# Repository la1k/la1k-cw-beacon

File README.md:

LA1K CW beacon project
======================

A 35-4400 MHz CW exciter design on a 75 x 45 mm 4-layer PCB. Will initially be used for a 70 MHz beacon in Norway (with a 25 W PA and an external 10 MHz OCXO), and eventually replace hardware in our existing 2m and 70cm beacons. A serial port is used for configuration of callsign, ramp time, frequency etc.

- **Microcontroller (Microchip PIC18F26K22):** Controls synthesizer, does CW timing, controls VGA gain.
- **Synthesizer (Analog Devices ADF4351):** Fractional-N synthesizer with VCO which generates the RF-signal. Only course control over output power.
- **VGA (Analog Devices ADL5330):** Amplifier with variable gain over a 60 dB span. Controlled by filtered PWM-signal from microcontroller and softens the keying transitions by controlling output power ramping. Also works as a buffer for an external PA.

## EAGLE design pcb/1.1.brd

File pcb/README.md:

- BOM is located in this folder in CSV and tab-separated formats. 
- Most components have vendor part numbers from Digi-Key.
- Reference oscillator FOX924B, C40 and C38 is typically not inserted if used with external oscillator, as there will be some leakage over the REF_SEL header even without a jumper installed.
- For PCB 1.0, remember to scratch away solder stop mask for U1 and U2 exposed pads.
- Use standard 0.1" / 2.54 mm pitch break-away headers for PIC_GPIO, PIC_UART, REF_SEL and PIC_REF.

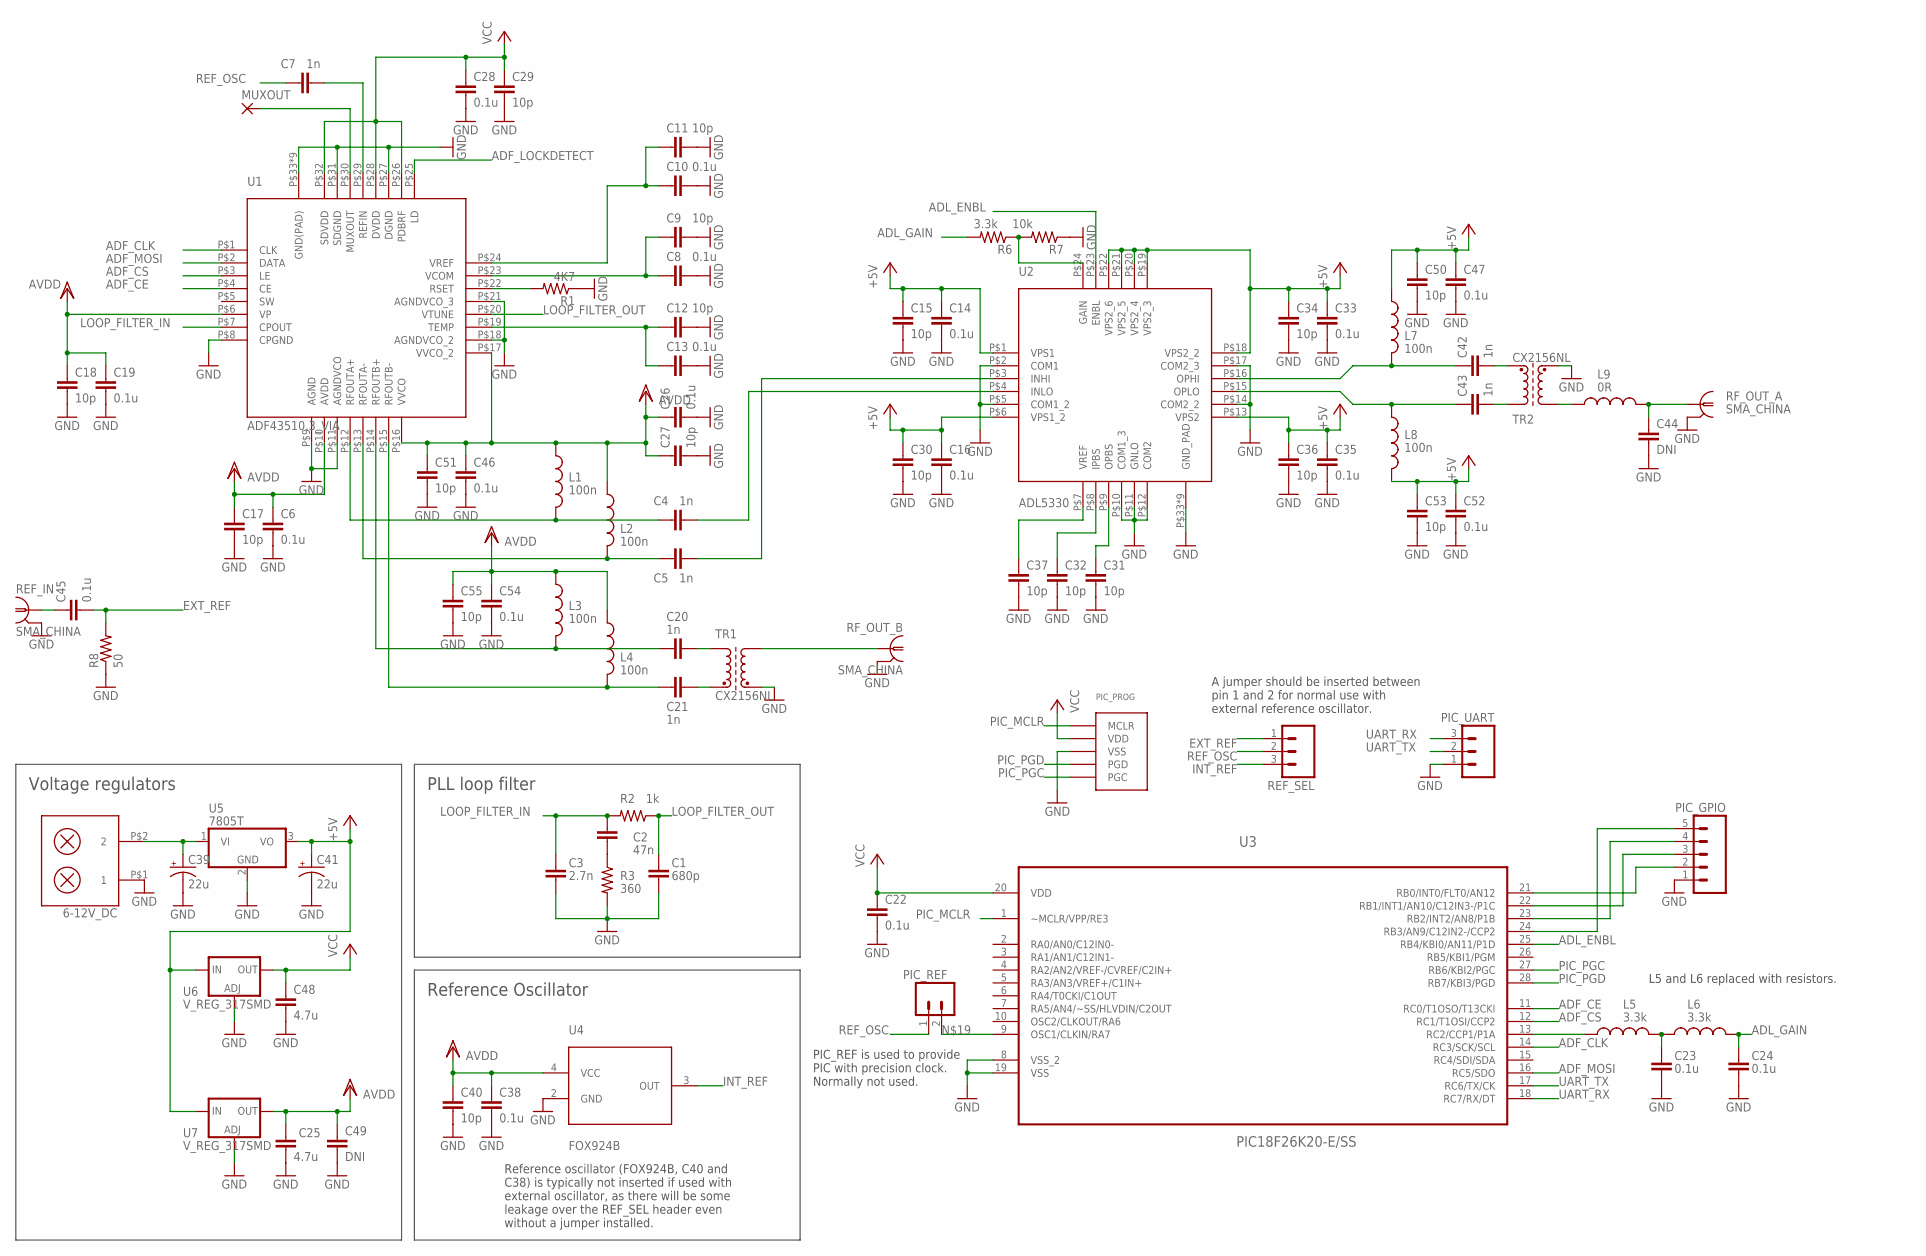
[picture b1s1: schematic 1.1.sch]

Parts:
6-12V_DC: PK5602; PARTNO 1984617
C1: 680p; 0603-CAP; PARTNO GRM1885C1H681JA01D
C2: 47n; 0603-CAP; PARTNO GRM188R71E473JA01D
C3: 2.7n; 0603-CAP; PARTNO GRM1885C1H272JA01D
C4, C5, C7, C20, C21: 1n; 0603-CAP; PARTNO GRM1885C1H102FA01D
C6, C8, C10, C13, C14, C16, C19, C22, C23, C24, C26, C28, C33, C35, C38, C45, C46, C47, C52, C54: 0.1u; 0603-CAP; PARTNO GRM188R71E104KA01D
C9, C11, C12, C15, C17, C18, C27, C29, C30, C31, C32, C34, C36, C37, C40, C50, C51, C53, C55: 10p; 0603-CAP; PARTNO GRM1885C1H100FA01D
C25, C48: 4.7u; C0805; PARTNO GRM21BR61E475KA12K
C39, C41: 22u; VISHAY_C; PARTNO TH4C226K016C1400
C42, C43: 1n; C0805K; PARTNO GRM1885C1H102FA01D
C44: DNI; C0805K; PARTNO *
C49: DNI; C0805; PARTNO *
L1, L2, L3, L4: 100n; 0603; PARTNO LQW18ANR10J00D
L5, L6: 3.3k; 0603; PARTNO MCR03ERTF3321
L7, L8: 100n; C0805K; PARTNO LQW18ANR10J00D
L9: 0R; C0805K; PARTNO *
MUXOUT: SMD2; SMD1,27-2,54; PARTNO *
PIC_GPIO: M05PTH; 1X05; PARTNO *
PIC_PROG: 1X5_ICSP; 1X5_2MM; PARTNO M22-2510505
PIC_REF: M02PTH; 1X02; PARTNO *
PIC_UART: M03PTH; 1X03; PARTNO *
R1: 4K7; 0603-RES; PARTNO MCR03ERTF4701
R2: 1k; 0603-RES; PARTNO MCR03ERTF1001
R3: 360; 0603-RES; PARTNO MCR03ERTF3600
R6: 3.3k; 0603-RES; PARTNO MCR03ERTF3321
R7: 10k; 0603-RES; PARTNO MCR03ERTF1002
R8: 50; C0805K; PARTNO ERJ-P06J510V
REF_IN: SMA_CHINA; SMA-EDGE; PARTNO SMA-J-P-H-ST-EM1
REF_SEL: M03PTH; 1X03; PARTNO *
RF_OUT_A: SMA_CHINA; SMA-EDGE; PARTNO SMA-J-P-H-ST-EM1
RF_OUT_B: SMA_CHINA; SMA-EDGE; PARTNO SMA-J-P-H-ST-EM1
TR1, TR2: CX2156NL; PARTNO CX2156NL
U1: ADF43510.3_VIA; LFCSP_CP-32-2_.3VIA; PARTNO ADF4351BCPZ-RL7
U2: ADL5330; LFCSP_CP-24-2_.3VIA; PARTNO ADL5330ACPZ-REEL7
U3: PIC18F26K20-E/SS; SOP65P780X200-28N; PARTNO PIC18F26K22-I/SS
U4: FOX924B; PARTNO *
U5: 7805T; TO220H; PARTNO LM7805CT
U6, U7: V_REG_317SMD; SOT223; PARTNO AP2114H-3.3TRG1

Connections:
+5V: C14.1, C15.1, C16.1, C30.1, C33.1, C34.1, C35.1, C36.1, C41.+, C47.1, C50.1, C52.1, C53.1, L7.1, L8.1, U2.P$1 (VPS1), U2.P$6 (VPS1_2), U2.P$13 (VPS2), U2.P$18 (VPS2_2), U2.P$19 (VPS2_3), U2.P$20 (VPS2_4), U2.P$21 (VPS2_5), U2.P$22 (VPS2_6), U5.3 (VO), U6.3 (IN), U7.3 (IN)
ADF_CE: U1.P$4 (CE), U3.11 (RC0/T1OSO/T13CKI)
ADF_CLK: U1.P$1 (CLK), U3.14 (RC3/SCK/SCL)
ADF_CS: U1.P$3 (LE), U3.12 (RC1/T1OSI/CCP2)
ADF_LOCKDETECT: U1.P$25 (LD)
ADF_MOSI: U1.P$2 (DATA), U3.16 (RC5/SDO)
ADF_MUXOUT: MUXOUT.1, U1.P$30 (MUXOUT)
ADL_ENBL: U2.P$23 (ENBL), U3.25 (RB4/KBI0/AN11/P1D)
ADL_GAIN: C24.2, L6.2, R6.2
EXT_REF: C45.2, R8.2, REF_SEL.1
GND: 6-12V_DC.P$1 (1), C1.2, C3.2, C6.2, C8.2, C9.2, C10.2, C11.2, C12.2, C13.2, C14.2, C15.2, C16.2, C17.2, C18.2, C19.2, C22.2, C23.1, C24.1, C25.2, C26.2, C27.2, C28.2, C29.2, C30.2, C31.2, C32.2, C33.2, C34.2, C35.2, C36.2, C37.2, C38.2, C39.-, C40.2, C41.-, C44.2, C46.2, C47.2, C48.2, C49.2, C50.2, C51.2, C52.2, C53.2, C54.2, C55.2, PIC_GPIO.1, PIC_PROG.P$3 (VSS), PIC_UART.1, R1.1, R3.2, R7.1, R8.1, REF_IN.GND@0 (GND), REF_IN.GND@1 (GND), REF_IN.GND@2 (GND), REF_IN.GND@3 (GND), RF_OUT_A.GND@0 (GND), RF_OUT_A.GND@1 (GND), RF_OUT_A.GND@2 (GND), RF_OUT_A.GND@3 (GND), RF_OUT_B.GND@0 (GND), RF_OUT_B.GND@1 (GND), RF_OUT_B.GND@2 (GND), RF_OUT_B.GND@3 (GND), TR1.5 (E2), TR2.5 (E2), U1.P$8 (CPGND), U1.P$9 (AGND), U1.P$11 (AGNDVCO), U1.P$18 (AGNDVCO_2), U1.P$21 (AGNDVCO_3), U1.P$27 (DGND), U1.P$31 (SDGND), U1.P$33 (GND(PAD)), U1.P$34 (GND(PAD)), U1.P$35 (GND(PAD)), U1.P$36 (GND(PAD)), U1.P$37 (GND(PAD)), U1.P$38 (GND(PAD)), U1.P$39 (GND(PAD)), U1.P$40 (GND(PAD)), U1.P$41 (GND(PAD)), U2.P$2 (COM1), U2.P$5 (COM1_2), U2.P$10 (COM1_3), U2.P$11 (GNLO), U2.P$12 (COM2), U2.P$14 (COM2_2), U2.P$17 (COM2_3), U2.P$33 (GND_PAD), U2.P$34 (GND_PAD), U2.P$35 (GND_PAD), U2.P$36 (GND_PAD), U2.P$37 (GND_PAD), U2.P$38 (GND_PAD), U2.P$39 (GND_PAD), U2.P$40 (GND_PAD), U2.P$41 (GND_PAD), U3.8 (VSS_2), U3.19 (VSS), U4.2 (GND), U5.2 (GND), U6.1 (ADJ), U7.1 (ADJ)
INT_REF: REF_SEL.3, U4.3 (OUT)
LOOP_FILTER_IN: C2.1, C3.1, R2.2, U1.P$7 (CPOUT)
LOOP_FILTER_OUT: C1.1, R2.1, U1.P$20 (VTUNE)
unnamed: C5.2, U2.P$3 (INHI)
unnamed: C4.2, U2.P$4 (INLO)
unnamed: C7.2, U1.P$29 (REFIN)
unnamed: L9.1, TR2.4 (A2)
unnamed: C42.1, L7.2, U2.P$16 (OPHI)
unnamed: R1.2, U1.P$22 (RSET)
unnamed: C43.1, L8.2, U2.P$15 (OPLO)
unnamed: C2.2, R3.1
unnamed: C5.1, L2.2, U1.P$13 (RFOUTA-)
unnamed: C4.1, L1.2, U1.P$12 (RFOUTA+)
unnamed: 6-12V_DC.P$2 (2), C39.+, U5.1 (VI)
unnamed: C43.2, TR2.3 (A1)
unnamed: C12.1, C13.1, U1.P$19 (TEMP)
unnamed: C8.1, C9.1, U1.P$23 (VCOM)
unnamed: PIC_GPIO.5, U3.24 (RB3/AN9/C12IN2-/CCP2)
unnamed: C42.2, TR2.1 (E1)
unnamed: PIC_GPIO.4, U3.23 (RB2/INT2/AN8/P1B)
unnamed: C20.1, L3.2, U1.P$14 (RFOUTB+)
unnamed: PIC_REF.2, U3.9 (OSC1/CLKIN/RA7)
unnamed: C10.1, C11.1, U1.P$24 (VREF)
unnamed: C21.1, L4.2, U1.P$15 (RFOUTB-)
unnamed: L5.1, U3.13 (RC2/CCP1/P1A)
unnamed: C21.2, TR1.1 (E1)
unnamed: C23.2, L5.2, L6.1
unnamed: C20.2, TR1.3 (A1)
unnamed: RF_OUT_B.SIG (1), TR1.4 (A2)
unnamed: C37.1, U2.P$7 (VREF)
unnamed: PIC_GPIO.3, U3.22 (RB1/INT1/AN10/C12IN3-/P1C)
unnamed: PIC_GPIO.2, U3.21 (RB0/INT0/FLT0/AN12)
unnamed: R6.1, R7.2, U2.P$24 (GAIN)
unnamed: C45.1, REF_IN.SIG (1)
unnamed: C31.1, U2.P$9 (OPBS)
unnamed: C32.1, U2.P$8 (IPBS)
unnamed: C44.1, L9.2, RF_OUT_A.SIG (1)
PIC_MCLR: PIC_PROG.P$1 (MCLR), U3.1 (~MCLR/VPP/RE3)
PIC_PGC: PIC_PROG.P$5 (PGC), U3.27 (RB6/KBI2/PGC)
PIC_PGD: PIC_PROG.P$4 (PGD), U3.28 (RB7/KBI3/PGD)
REF_OSC: C7.1, PIC_REF.1, REF_SEL.2
UART_RX: PIC_UART.3, U3.18 (RC7/RX/DT)
UART_TX: PIC_UART.2, U3.17 (RC6/TX/CK)
VCC: C22.1, C28.1, C29.1, C48.1, PIC_PROG.P$2 (VDD), U1.P$26 (PDBRF), U1.P$28 (DVDD), U1.P$32 (SDVDD), U3.20 (VDD), U6.2 (OUT)
VDD: C6.1, C17.1, C18.1, C19.1, C25.1, C26.1, C27.1, C38.1, C40.1, C46.1, C49.1, C51.1, C54.1, C55.1, L1.1, L2.1, L3.1, L4.1, U1.P$6 (VP), U1.P$10 (AVDD), U1.P$16 (VVCO), U1.P$17 (VVCO_2), U4.4 (VCC), U7.2 (OUT)

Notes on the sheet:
PLL loop filter
Reference Oscillator
Voltage regulators
L5 and L6 replaced with resistors.
PIC_REF is used to provide PIC with precision clock. Normally not used.
A jumper should be inserted between pin 1 and 2 for normal use with external reference oscillator.
Reference oscillator (FOX924B, C40 and C38) is typically not inserted if used with external oscillator, as there will be some leakage over the REF_SEL header even without a jumper installed.

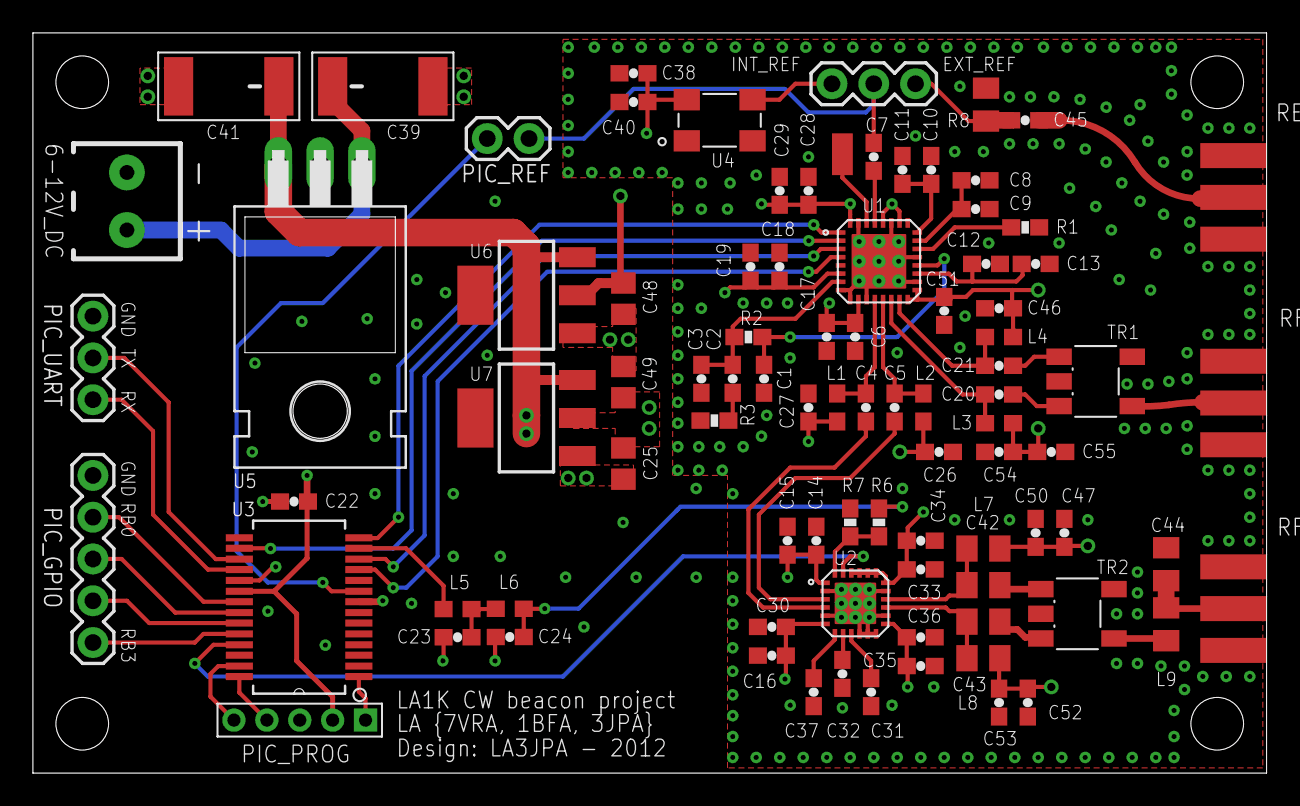
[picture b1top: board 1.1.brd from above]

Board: 4 copper layers, 75.0 x 45.0 mm, 89 parts (0 on the bottom side), 55 nets.

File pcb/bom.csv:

Mfg_PN,Mfg,Vendor_PN,Vendor,Description,Qty-1,Qty-5,Qty-25,Part References,Value
GRM188R71E104KA01D,Murata,490-1524-1-ND,Digikey,CAP CER 0.1UF 25V 10% X7R 0603,20,100,500,"C6, C8, C10, C13, C14, C16, C19, C22, C23, C24, C26, C28, C33, C35, C38, C45, C46, C47, C52, C54",0.1u
M22-2510505,Harwin,952-1314-ND,Digikey,CONN HEADER 2MM VERT AU 5POS,1,5,25,"PIC_PROG",1X5_ICSP
MCR03ERTF1001,Rohm,RHM1.00KCFCT-ND,Digikey,RES 1K OHM 1/10W 1% 0603 SMD,1,5,25,"R2",1k
GRM1885C1H102FA01D,Murata,490-6376-1-ND,Digikey,CAP CER 1000pF 50V 0603,2,10,50,"C42, C43",1n
GRM1885C1H102FA01D,Murata,490-6376-1-ND,Digikey,CAP CER 1000pF 50V 0603,5,25,125,"C4, C5, C7, C20, C21",1n
GRM1885C1H272JA01D,Murata,490-3283-1-ND,Digikey,CAP CER 2700pF 50V 0603,1,5,25,"C3",2.7n
MCR03ERTF3321,Rohm,RHM3.32KCFCT-ND,Digikey,RES 3.32K OHM 1/10W 1% 0603 SMD,2,10,50,"L5, L6",3.3k
MCR03ERTF3321,Rohm,RHM3.32KCFCT-ND,Digikey,RES 3.32K OHM 1/10W 1% 0603 SMD,1,5,25,"R6",3.3k
GRM21BR61E475KA12K,Murata,490-6475-1-ND,Digikey,CAP CER 4.7UF 25V 10% X5R 0805,2,10,50,"C25, C48",4.7u
MCR03ERTF4701,Rohm,RHM4.70KCFCT-ND,Digikey,RES 4.7K OHM 1/10W 1% 0603 SMD,1,5,25,"R1",4K7
MCR03ERTF1002,Rohm,RHM10.0KCFCT-ND,Digikey,RES 10K OHM 1/10W 1% 0603 SMD,1,5,25,"R7",10k
GRM1885C1H100FA01D,Murata,490-9713-1-ND,Digikey,CAP CER 10pF 50V 0603,19,95,475,"C9, C11, C12, C15, C17, C18, C27, C29, C30, C31, C32, C34, C36, C37, C40, C50, C51, C53, C55",10p
TH4C226K016C1400,Vishay,718-1911-1-ND,Digikey,22µF Molded Tantalum Capacitors 16V 2413,2,10,50,"C39, C41",22u
GRM188R71E473JA01D,Murata,490-11528-1-ND,Digikey,CAP CER 0.047µF 25V 0603,1,5,25,"C2",47n
ERJ-P06J510V,Panasonic,P51ADCT-ND,Digikey,RES SMD 51 OHM 5% 1/2W 0805,1,5,25,"R8",50
LQW18ANR10J00D,Murata,490-1179-1-ND,Digikey,INDUCTOR 100nH Unshielded Wirewound Inductor 220mA 680 mOhm Max 0603,2,10,50,"L7, L8",100n
LQW18ANR10J00D,Murata,490-1179-1-ND,Digikey,INDUCTOR 100nH Unshielded Wirewound Inductor 220mA 680 mOhm Max 0603,4,20,100,"L1, L2, L3, L4",100n
MCR03ERTF3600,Rohm,RHM360CFCT-ND,Digikey,RES SMD 360 OHM 1% 1/10W 0603,1,5,25,"R3",360
GRM1885C1H681JA01D,Murata,490-1447-1-ND,Digikey,CAP CER 680pF 50 0603,1,5,25,"C1",680p
LM7805CT,Fairchild,LM7805CT-ND,Digikey,Linear Voltage Regulator IC Positive Fixed 1 Output 5V 1A TO-220AB,1,5,25,"U5",7805T
ADF4351BCPZ-RL7,Analog Devices,ADF4351BCPZ-RL7CT-ND,Digikey,IC SYNTH PLL VCO 32LFCSP,1,5,25,"U1",ADF43510.3_VIA
ADL5330ACPZ-REEL7,Analog Devices,ADL5330ACPZ-REEL7CT-ND,Digikey,RF Amplifier IC,1,5,25,"U2",ADL5330
CX2156NL,Pulse,553-1499-ND,Digikey,RF Balun 2.3MHz ~ 2.7GHz 1:1 5-SMD,2,10,50,"TR1, TR2",CX2156NL
PIC18F26K22-I/SS,Microchip Technology,PIC18F26K22-I/SS-ND,Digikey,IC MCU 8BIT 64KB FLASH 28SSOP,1,5,25,"U3",PIC18F26K20-E/SS
1984617,Phoenix,277-1721-ND,Digikey,2 Position Wire to Board Terminal Block Horizontal with Board 0.138" (3.50mm) Through Hole,1,5,25,"6-12V_DC",PK5602
SMA-J-P-H-ST-EM1,Samtec,SAM8857-ND,Digikey,SMA Connector Jack, Female Socket 50 Ohm Board Edge, End Launch Solder,3,15,75,"REF_IN, RF_OUT_A, RF_OUT_B",SMA_CHINA
AP2114H-3.3TRG1,Diodes Inc,AP2114H-3.3TRG1DICT-ND,Digikey,Linear Voltage Regulator IC Positive Fixed 1 Output 3.3V 1A SOT-223,2,10,50,"U6, U7",V_REG_317SMD
*** ERROR - PART '*' NOT FOUND FOR: "PIC_REF"
*** ERROR - PART '*' NOT FOUND FOR: "PIC_UART, REF_SEL"
*** ERROR - PART '*' NOT FOUND FOR: "PIC_GPIO"
*** ERROR - PART '*' NOT FOUND FOR: "MUXOUT"
*** ERROR - PART '*' NOT FOUND FOR: "C49"
*** ERROR - PART '*' NOT FOUND FOR: "C44"
*** ERROR - PART '*' NOT FOUND FOR: "U4"
*** ERROR - PART '*' NOT FOUND FOR: "L9"

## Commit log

2015-07-30 - Fixed scheduler bug where execution stops after 2^31 ms - Added button support (stop keying, key manually) - UART buffer overflow behavior changed (throws away data rather than blocking further exe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
2016-10-04 Added BOM and updated schematic.

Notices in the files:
parts and their libraries:
SparkFun: Licensing: CC v3.0 Share-Alike You are welcome to use this library for commercial purposes.
